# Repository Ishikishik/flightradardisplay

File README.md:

# フライトレーダー表示プロジェクト
ご自宅で受信しているADS-Bの情報をいい感じの可愛いディスプレイに映す

# フォルダ構成と補足情報
## firm
- esp32に書き込む情報(PlatformIOで開発)
### 手順
1. maketable.pyを使ってtable(地図データ、航空会社・国の対応表、国旗・航空会社の画像)を作る
   - 著作権の関係から画像は載っていません。`python maketable.py --images` で取得してから `python maketable.py` を実行
1. `firm/src/secret.h` を以下のように作る
```cpp
const char* WIFI_LIST[][2] = {{"SSID", "パスワード"}};   // 上にあるものから優先
#define WS_HOST "サーバーのホスト名"
#define WS_PORT 443
#define WS_PATH "/?token=トークン"
```
1. `firm/src/config.h` をいい感じに編集(地図の範囲など)
1. `pio run -e v2 -t upload` で書き込む
### 操作
- 押し込み: 地図と一覧の切り替え / 長押し: スリープ
- 左右: 機体の選択・ページ送り / 左右どちらかの長押し: 光でWi-Fi設定([otter-device-link](https://github.com/Ishikishik/otter-device-link))
## pcb
- 銅箔の情報
- 単三2本かtype-cで給電(typec側を優先する回路付き)
## hard
- 外装
- カメラと同じネジで固定可能
## server
- ご自宅のラズパイが呟くadsb情報jsonをバイナリ形式にしてwebsocketで呟く(プロトコルは[こちら](/server/PROTOCOL.md))

# おせわになりました。
- [ICAOから航空会社、国を特定する部分](https://raw.githubusercontent.com/vradarserver/standing-data/main/)
  - Virtual Radar Server standing-data(CC0)
- [航空会社の画像](https://github.com/anhthang/soaring-symbols)
  - soaring-symbols(MIT)。尾翼マーク・社名ロゴの SVG
- [航空会社の画像(追加分)](https://github.com/Jxck-S/airline-logos)
  - Jxck-S/airline-logos。soaring-symbols にない会社を補完
- [国旗の画像](https://flagcdn.com)
  - flagcdn.com
- [地図(海岸線)](https://www.naturalearthdata.com)
  - Natural Earth(パブリックドメイン)のデータを cartopy で描画して作成
- [液晶の描画](https://github.com/lovyan03/LovyanGFX)
  - LovyanGFX
- [WebSocket(ESP32 側)](https://github.com/Links2004/arduinoWebSockets)
  - arduinoWebSockets
- [WebSocket(サーバー側)](https://github.com/python-websockets/websockets)
  - websockets(Python)

航空会社のロゴは各社の商標・著作物です。このリポジトリには含めていません(`firm/maketable/images/` は中身を git 管理外にしています)。必要な場合は `maketable.py --images` で各自取得してください。

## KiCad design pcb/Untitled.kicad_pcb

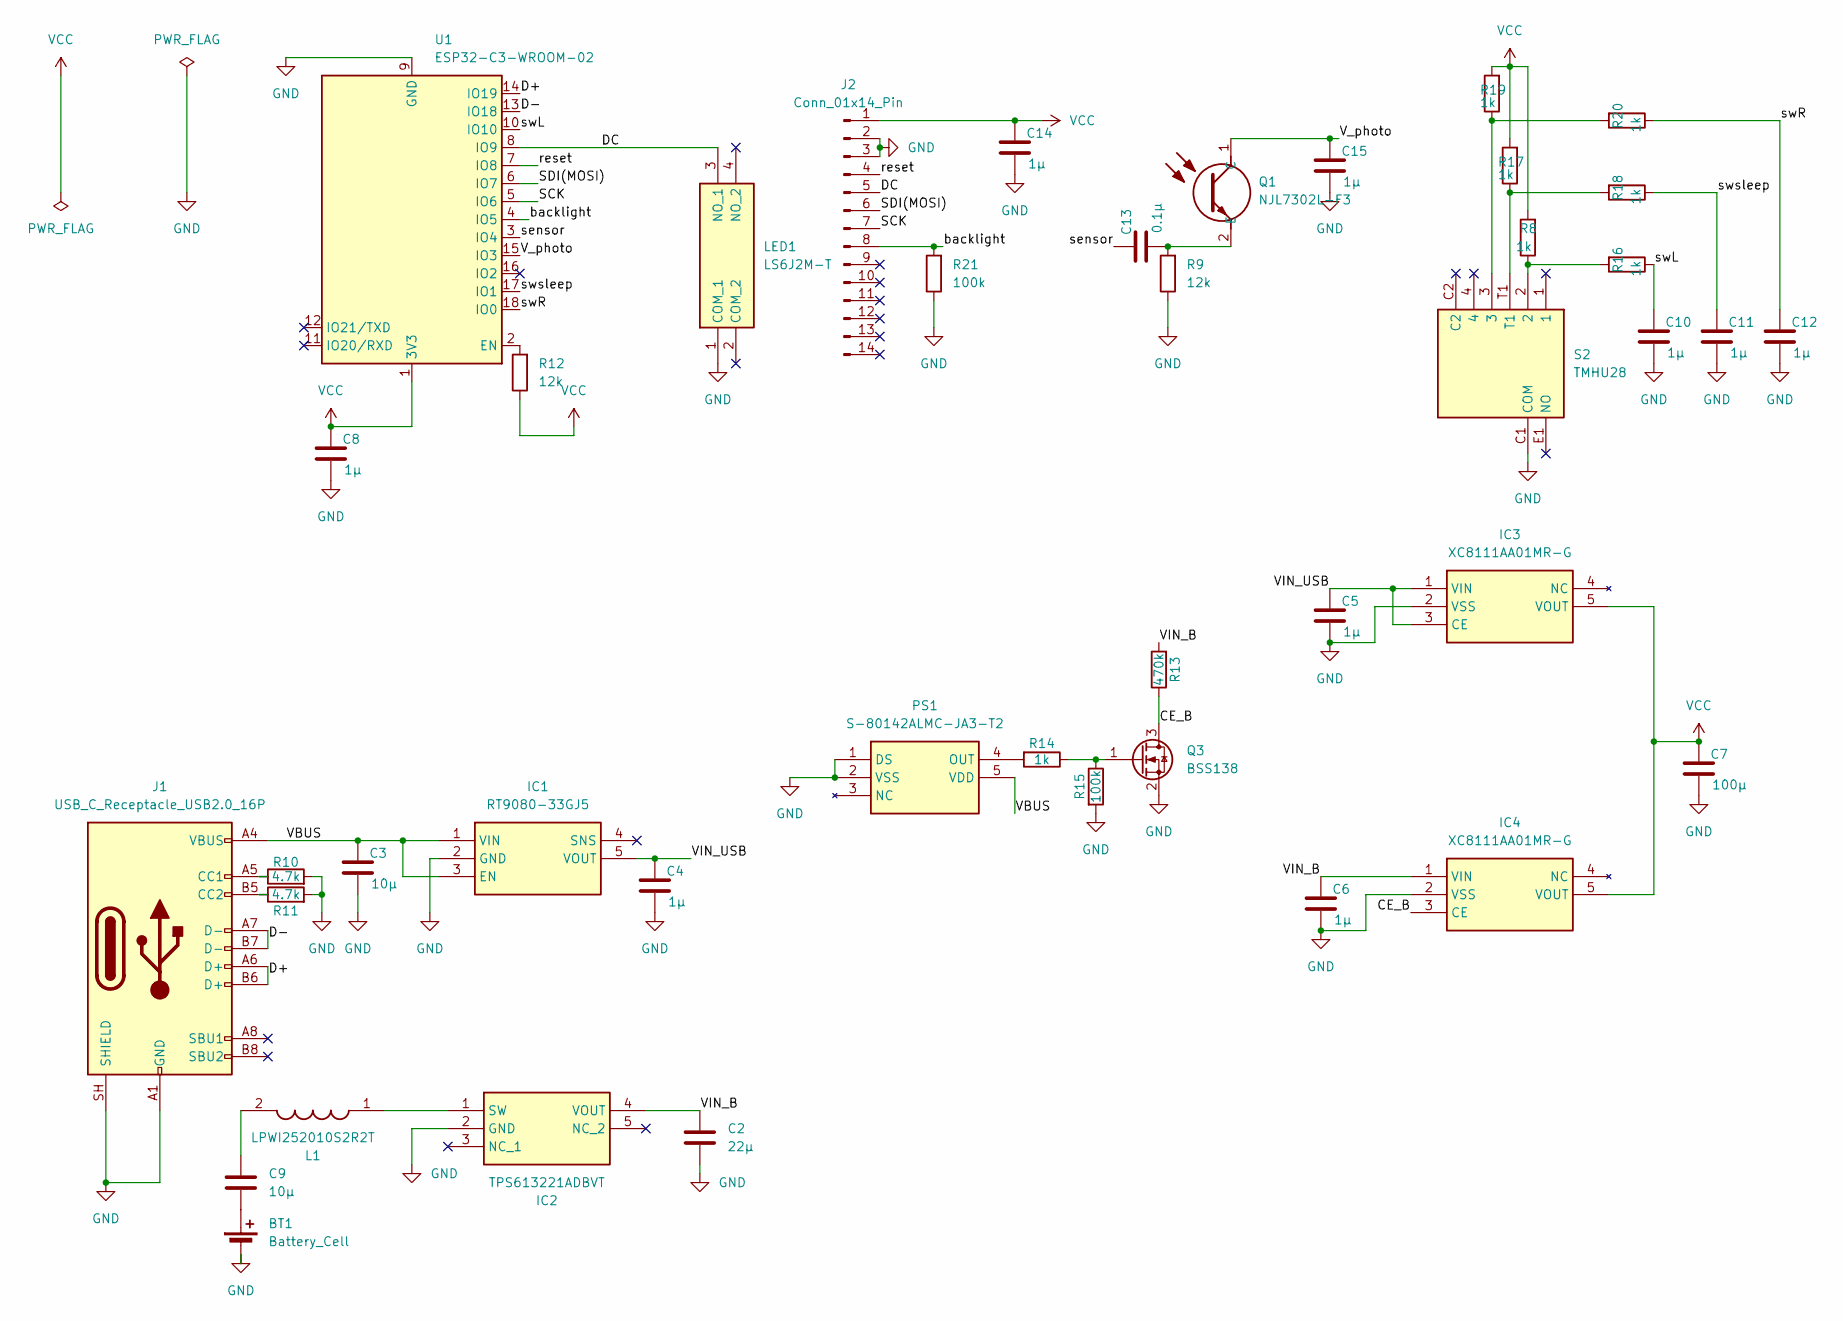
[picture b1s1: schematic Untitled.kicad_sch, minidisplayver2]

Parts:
BT1: Battery_Cell; BH-321-2P
C2: 22μ; C_0603_1608Metric_Pad1.08x0.95mm_HandSolder
C3: 10μ; C_0402_1005Metric
C4, C5, C6, C8, C10, C11, C12, C14, C15: 1μ; C_0402_1005Metric
C7: 100μ; C_1206_3216Metric
C9: 10μ; C_0603_1608Metric_Pad1.08x0.95mm_HandSolder
C13: 0.1μ; C_0402_1005Metric
IC1: RT9080-33GJ5; SOT94P280X100-5N; Manufacturer_Part_Number RT9080-33GJ5; Mouser Part Number 835-RT9080-33GJ5
IC2: TPS613221ADBVT; SOT95P280X145-5N; Manufacturer_Part_Number TPS613221ADBVT; Mouser Part Number 595-TPS613221ADBVT
IC3, IC4: XC8111AA01MR-G; SOT95P280X130-5N; Manufacturer_Part_Number XC8111AA01MR-G; Mouser Part Number 865-XC8111AA01MR-G
J1: USB_C_Receptacle_USB2.0_16P; USB_C_Receptacle_GCT_USB4105-xx-A_16P_TopMnt_Horizontal
J2: Conn_01x14_Pin; MSP2807
L1: LPWI252010S2R2T; INDC2520X100N; Manufacturer_Part_Number LPWI252010S2R2T; Mouser Part Number 576-LPWI252010S2R2T
LED1: LS6J2M-T; LS6J2MT; Manufacturer_Part_Number LS6J2M-T
PS1: S-80142ALMC-JA3-T2; SOT95P275X130-5N; Manufacturer_Part_Number S-80142ALMC-JA3-T2
Q1: NJL7302L-F3; NJL7302LF3; Manufacturer_Part_Number NJL7302L-F3; Mouser Part Number 513-NJL7302L-F3
Q3: BSS138; SOT-23
R8, R14, R16, R17, R18, R19, R20: 1k; R_0402_1005Metric
R9, R12: 12k; R_0402_1005Metric
R10, R11: 4.7k; R_0402_1005Metric
R13: 470k; R_0402_1005Metric
R15, R21: 100k; R_0402_1005Metric
S2: TMHU28; Manufacturer_Part_Number TMHU28
U1: ESP32-C3-WROOM-02

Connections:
/CE_B: IC4.3 (CE), Q3.3 (D), R13.1
/D+: J1.A6 (D+), J1.B6 (D+), U1.14 (IO19)
/D-: J1.A7 (D-), J1.B7 (D-), U1.13 (IO18)
/DC: J2.5 (T), LED1.3 (NO_1), U1.8 (IO9)
/SCK: J2.7 (LED), U1.5 (IO6)
/SDI(MOSI): J2.6 (MISO), U1.6 (IO7)
/VBUS: C3.1, IC1.1 (VIN), IC1.3 (EN), J1.A4 (VBUS), J1.A9 (VBUS), J1.B4 (VBUS), J1.B9 (VBUS), PS1.5 (VDD)
/VIN_B: C2.1, C6.1, IC2.4 (VOUT), IC4.1 (VIN), R13.2
/VIN_USB: C4.1, C5.1, IC1.5 (VOUT), IC3.1 (VIN), IC3.3 (CE)
/V_photo: C15.1, Q1.1 (C), U1.15 (IO3)
/backlight: J2.8 (SCK), R21.2, U1.4 (IO5)
/reset: J2.4, U1.7 (IO8)
/sensor: C13.1, U1.3 (IO4)
/swL: C10.1, R16.1, U1.10 (IO10)
/swR: C12.1, R20.1, U1.18 (IO0)
/swsleep: C11.1, R18.1, U1.17 (IO1)
GND: BT1.2 (-), C2.2, C3.2, C4.2, C5.2, C6.2, C7.2, C8.2, C10.2, C11.2, C12.2, C14.2, C15.2, IC1.2 (GND), IC2.2 (GND), IC3.2 (VSS), IC4.2 (VSS), J1.A1 (GND), J1.A12 (GND), J1.B1 (GND), J1.B12 (GND), J1.SH (SHIELD), J2.2, J2.3, LED1.1 (COM_1), PS1.1 (DS), PS1.2 (VSS), Q3.2 (S), R9.1, R10.2, R11.2, R15.2, R21.1, S2.C1 (COM), U1.9 (GND), U1.19 (GND)
unnamed: BT1.1 (+), C9.2
unnamed: C9.1, L1.2
unnamed: IC2.1 (SW), L1.1
unnamed: J1.A5 (CC1), R10.1
unnamed: J1.B5 (CC2), R11.1
unnamed: PS1.4 (OUT), R14.2
unnamed: C13.2, Q1.2 (E), R9.2
unnamed: Q3.1 (G), R14.1, R15.1
unnamed: R8.1, R16.2, S2.2
unnamed: R17.1, R18.2, S2.T1
unnamed: R19.1, R20.2, S2.3
unnamed: R12.2, U1.2 (EN)
VCC: C7.1, C8.1, C14.1, IC3.5 (VOUT), IC4.5 (VOUT), J2.1, R8.2, R12.1, R17.2, R19.2, U1.1 (3V3)

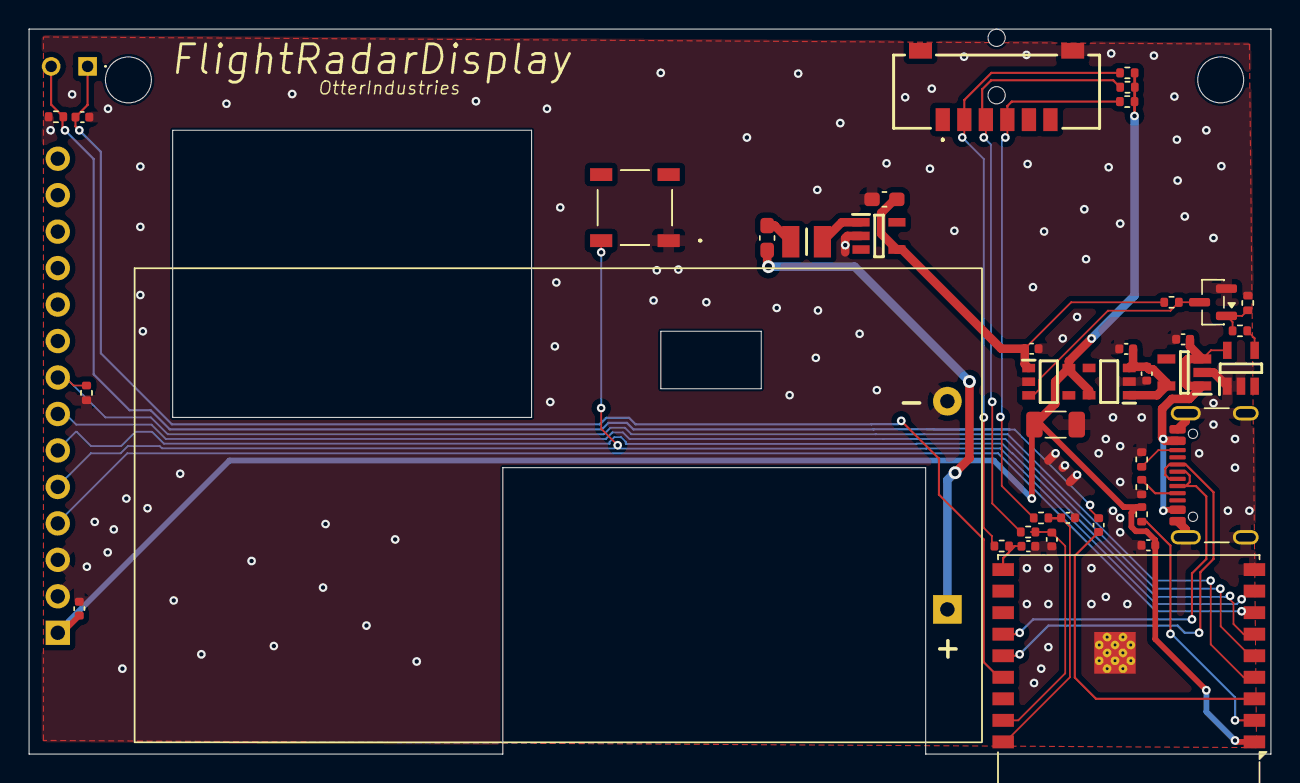
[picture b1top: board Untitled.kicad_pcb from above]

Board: 2 copper layers, 86.5 x 50.5 mm, 42 parts (1 on the bottom side), 30 nets.

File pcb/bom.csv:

"Reference","Qty","Value","DNP","Exclude from BOM","Exclude from Board","Footprint","Datasheet"
"BT1","1","Battery_Cell","","","","BH-321-2P:BH-321-2P",""
"C2","1","22μ","","","","Capacitor_SMD:C_0603_1608Metric_Pad1.08x0.95mm_HandSolder",""
"C3","1","10μ","","","","Capacitor_SMD:C_0402_1005Metric",""
"C4,C5,C6,C8,C10,C11,C12,C14,C15","9","1μ","","","","Capacitor_SMD:C_0402_1005Metric",""
"C7","1","100μ","","","","Capacitor_SMD:C_1206_3216Metric",""
"C9","1","10μ","","","","Capacitor_SMD:C_0603_1608Metric_Pad1.08x0.95mm_HandSolder",""
"C13","1","0.1μ","","","","Capacitor_SMD:C_0402_1005Metric",""
"IC1","1","RT9080-33GJ5","","","","RT9080-33GJ5:SOT94P280X100-5N","https://www.richtek.com/assets/product_file/RT9080/DS9080-05.pdf"
"IC2","1","TPS613221ADBVT","","","","TPS613221ADBVT:SOT95P280X145-5N","http://www.ti.com/lit/gpn/TPS61322"
"IC3,IC4","2","XC8111AA01MR-G","","","","XC8111AA01MR-G:SOT95P280X130-5N","https://www.torexsemi.com/file/xc8110/XC8110.pdf"
"J1","1","USB_C_Receptacle_USB2.0_16P","","","","Connector_USB:USB_C_Receptacle_GCT_USB4105-xx-A_16P_TopMnt_Horizontal","https://www.usb.org/sites/default/files/documents/usb_type-c.zip"
"J2","1","Conn_01x14_Pin","","","","MSP2807:MSP2807",""
"L1","1","LPWI252010S2R2T","","","","LPWI252010S2R2T:INDC2520X100N","https://www.arrow.com/en/products/lpwi252010s2r2t/littelfuse"
"LED1","1","LS6J2M-T","","","","LS6J2M-T:LS6J2MT",""
"PS1","1","S-80142ALMC-JA3-T2","","","","S-80142ALMC-JA3-T2:SOT95P275X130-5N","https://4donline.ihs.com/images/VipMasterIC/IC/SIIS/SIISS033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"
"Q1","1","NJL7302L-F3","","","","NJL7302L-F3:NJL7302LF3","https://www.nisshinbo-microdevices.co.jp/en/pdf/datasheet/NJ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"
"Q3","1","BSS138","","","","Package_TO_SOT_SMD:SOT-23","https://www.onsemi.com/pub/Collateral/BSS138-D.PDF"
"R8,R14,R16,R17,R18,R19,R20","7","1k","","","","Resistor_SMD:R_0402_1005Metric",""
"R9,R12","2","12k","","","","Resistor_SMD:R_0402_1005Metric",""
"R10,R11","2","4.7k","","","","Resistor_SMD:R_0402_1005Metric",""
"R13","1","470k","","","","Resistor_SMD:R_0402_1005Metric",""
"R15,R21","2","100k","","","","Resistor_SMD:R_0402_1005Metric",""
"S2","1","TMHU28","","","","TMHU28:TMHU28","http://en.jian-fu.com/product/content?id=664"
"U1","1","ESP32-C3-WROOM-02","","","","RF_Module:ESP32-C3-WROOM-02","https://www.espressif.com/sites/default/files/documentation/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"

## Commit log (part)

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2025-06-21 displayに映すまで
2025-06-21 背景に日本地図を描写
2025-06-23 地図を修正
2025-06-26 飛行機を映す関数を作成
2025-09-24 spriteを作る手前
2025-09-25 Remove secret.hpp
2025-09-27 地図と飛行機の位置を同時に表示
2025-09-27 地図と飛行機の位置を同時に表示(ダブルバッファあんまうまくいってない)
2025-09-27 underのサイズを微調整
2025-09-27 新たなスプライトに書き込むように変更
2025-09-27 ボタンが使えるように追加
2025-09-27 showjsonのちらつきを改善
2025-09-27 参考画像、readme.mdを更新
2025-09-27 キャッシュを消去
2025-09-29 read.mdに画像を追加
2025-10-18 外部で動かせる様に設定を追加＋wifi接続状態を表示するよう仕様変更
2025-10-20 readmeにrepeaterについて記載
